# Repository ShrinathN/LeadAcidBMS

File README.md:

# LeadAcidBMS
A BMS for my lead acid battery.

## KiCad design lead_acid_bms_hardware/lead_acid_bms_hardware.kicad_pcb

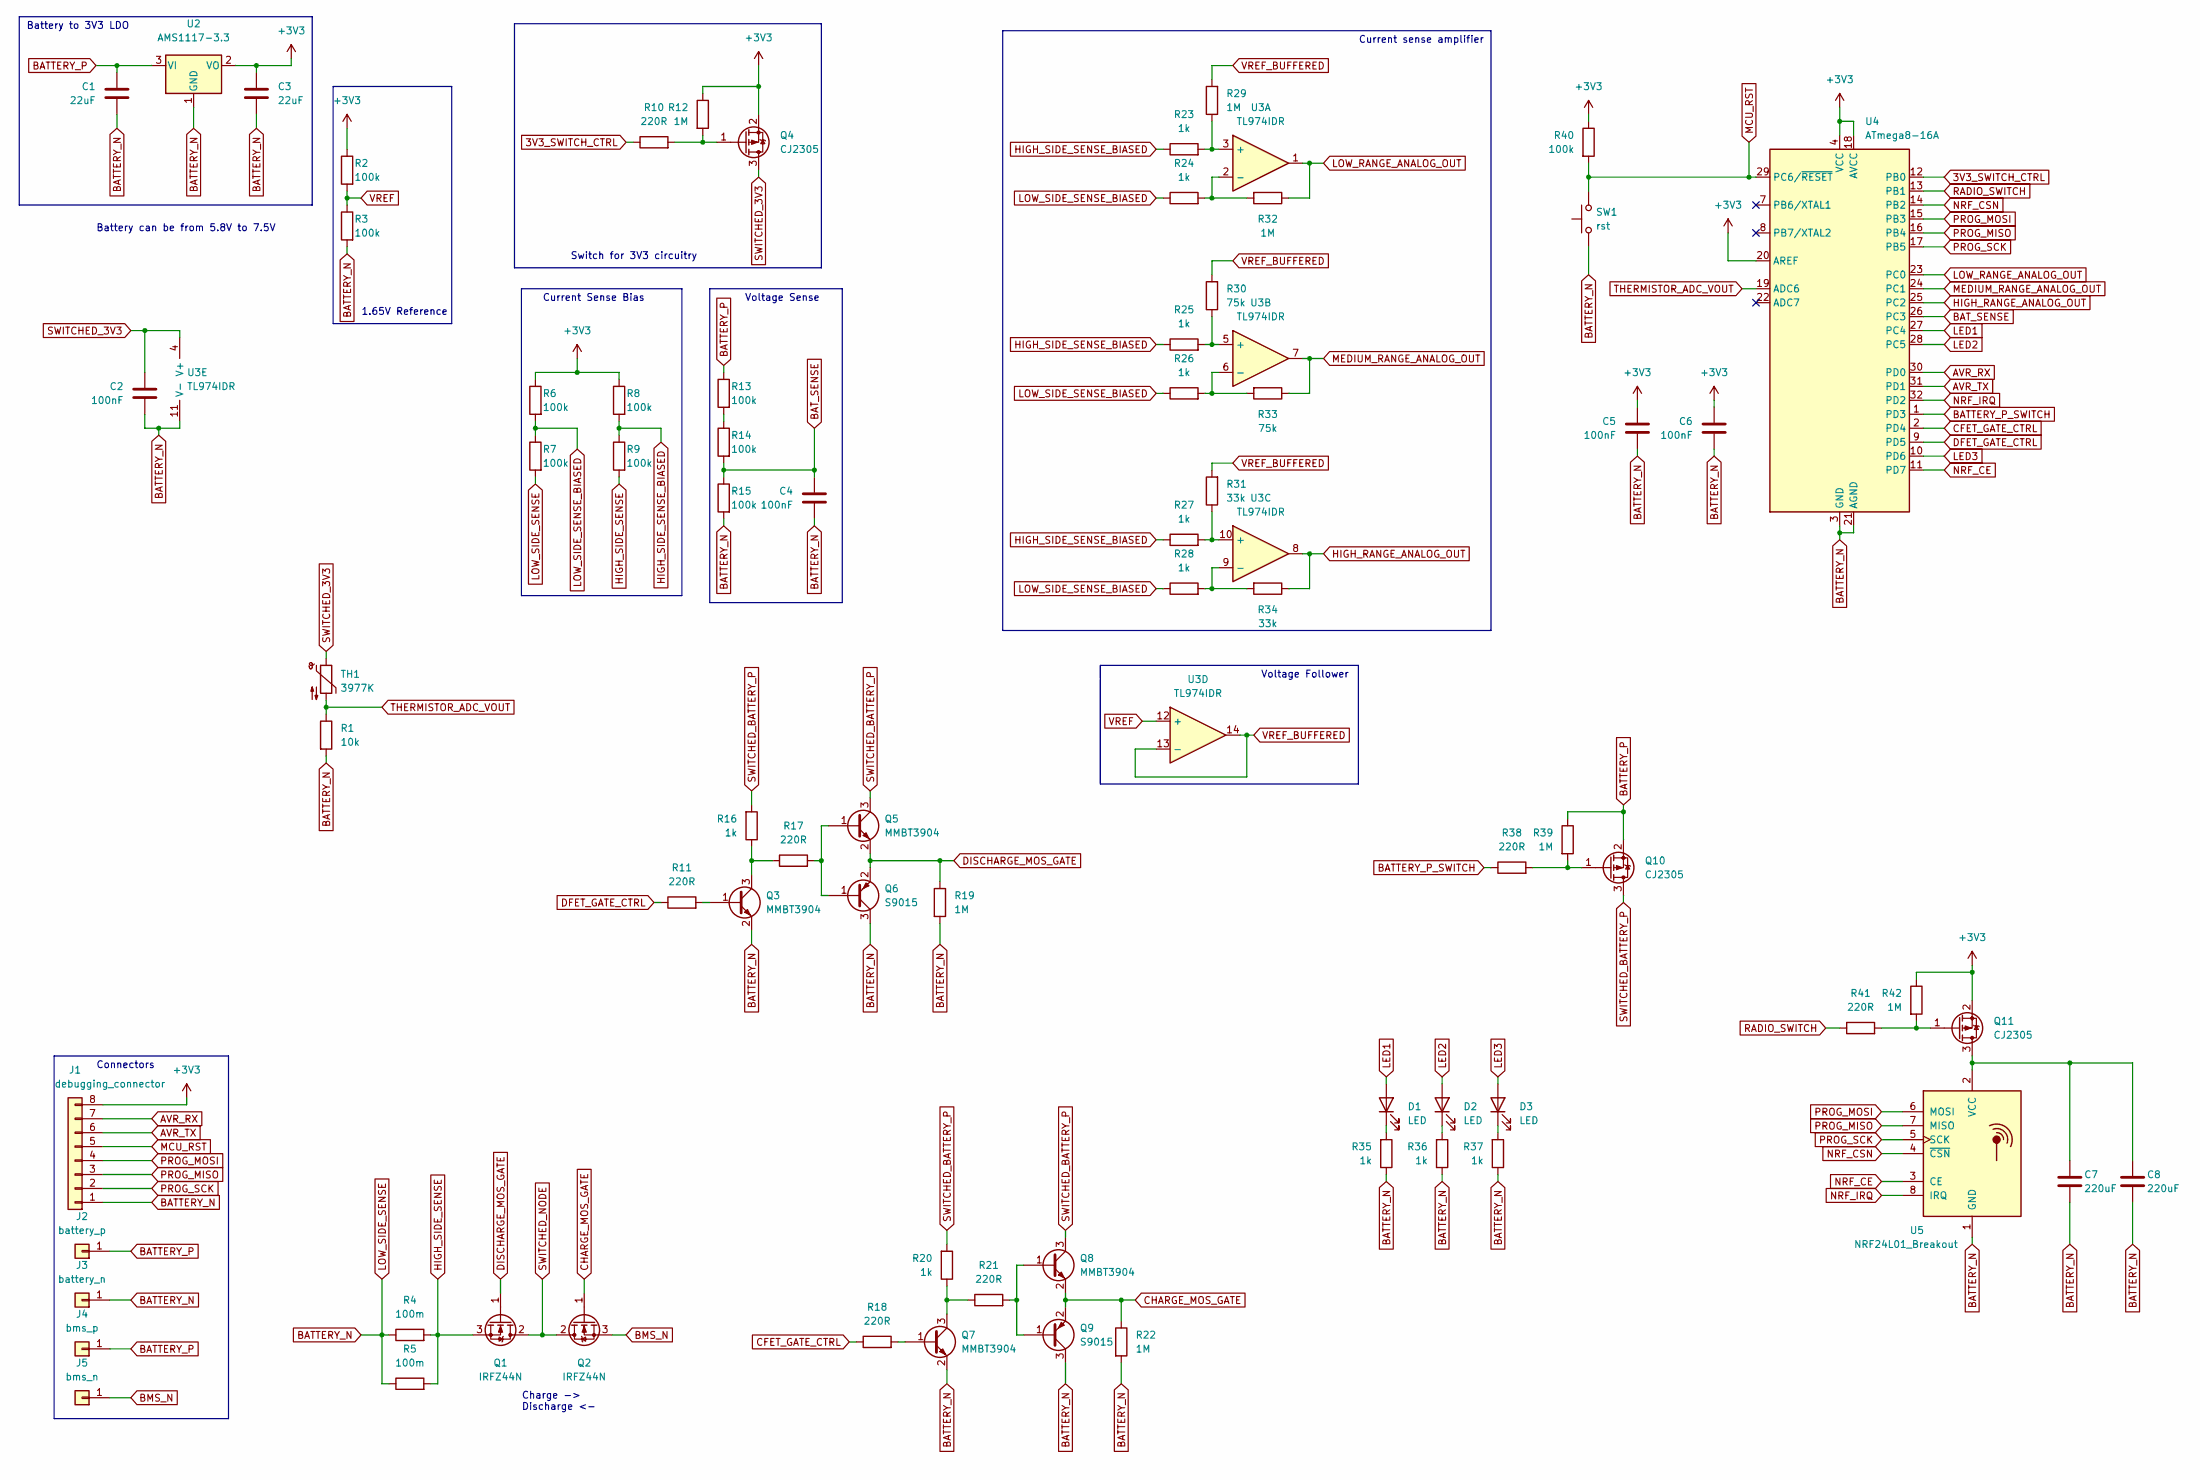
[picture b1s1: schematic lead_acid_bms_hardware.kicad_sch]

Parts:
C1, C3: 22uF; C_Radial_D5.0mm_H11.0mm_P2.00mm
C2, C4, C5, C6: 100nF; C_0805_2012Metric
C7, C8: 220uF; C_Radial_D6.3mm_H11.0mm_P2.50mm
D1, D2, D3: LED; LED_1206_3216Metric
J1: debugging_connector; PinHeader_1x08_P2.54mm_Vertical
J2: battery_p; MountingHole_3.2mm_M3_DIN965_Pad_TopBottom
J3: battery_n; MountingHole_3.2mm_M3_DIN965_Pad_TopBottom
J4: bms_p; MountingHole_3.2mm_M3_DIN965_Pad_TopBottom
J5: bms_n; MountingHole_3.2mm_M3_DIN965_Pad_TopBottom
Q1, Q2: IRFZ44N; TO-220-3_Horizontal_TabDown
Q3, Q5, Q7, Q8: MMBT3904; SOT-23
Q4, Q10, Q11: CJ2305; SOT-23
Q6, Q9: S9015; SOT-23
R1: 10k; R_0805_2012Metric
R2, R3, R6, R7, R8, R9, R13, R14, R15, R40: 100k; R_0805_2012Metric
R4, R5: 100m; R_2512_6332Metric
R10, R11, R17, R18, R21, R38, R41: 220R; R_0805_2012Metric
R12, R19, R22, R29, R32, R39, R42: 1M; R_0805_2012Metric
R16, R20, R23, R24, R25, R26, R27, R28, R35, R36, R37: 1k; R_0805_2012Metric
R30, R33: 75k; R_0805_2012Metric
R31, R34: 33k; R_0805_2012Metric
SW1: rst; SW_SPST_TL3342
TH1: 3977K; PinSocket_1x02_P2.54mm_Vertical
U2: AMS1117-3.3; SOT-223-3_TabPin2
U3: TL974IDR; TSSOP-14_4.4x5mm_P0.65mm
U4: ATmega8-16A; TQFP-32_7x7mm_P0.8mm
U5: NRF24L01_Breakout; nRF24L01_Breakout

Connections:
3V3_SWITCH_CTRL: R10.1, U4.12 (PB0)
+3V3: C3.1, C5.2, C6.2, J1.8, Q4.2 (S), Q11.2 (S), R2.1, R6.1, R8.1, R12.1, R40.1, R42.1, U2.2 (VO), U4.4 (VCC), U4.6 (VCC), U4.18 (AVCC), U4.20 (AREF)
AVR_RX: J1.7, U4.30 (PD0)
AVR_TX: J1.6, U4.31 (PD1)
BATTERY_N: C1.1, C2.1, C3.2, C4.1, C5.1, C6.1, C7.2, C8.2, J1.1, J3.1, Q3.2 (E), Q6.3 (C), Q7.2 (E), Q9.3 (C), R1.2, R3.2, R4.1, R5.1, R7.2, R15.2, R19.2, R22.2, R35.1, R36.1, R37.1, SW1.1, U2.1 (GND), U3.11 (V-), U4.3 (GND), U4.5 (GND), U4.21 (AGND), U5.1 (GND)
BATTERY_P: C1.2, J2.1, J4.1, Q10.2 (S), R13.1, R39.1, U2.3 (VI)
BATTERY_P_SWITCH: R38.1, U4.1 (PD3)
BAT_SENSE: C4.2, R14.2, R15.1, U4.26 (PC3)
BMS_N: J5.1, Q2.3 (S)
CFET_GATE_CTRL: R18.1, U4.2 (PD4)
CHARGE_MOS_GATE: Q2.1 (G), Q8.2 (E), Q9.2 (E), R22.1
DFET_GATE_CTRL: R11.1, U4.9 (PD5)
DISCHARGE_MOS_GATE: Q1.1 (G), Q5.2 (E), Q6.2 (E), R19.1
HIGH_RANGE_ANALOG_OUT: R34.1, U3.8, U4.25 (PC2)
HIGH_SIDE_SENSE: Q1.3 (S), R4.2, R5.2, R9.2
HIGH_SIDE_SENSE_BIASED: R8.2, R9.1, R23.1, R25.1, R27.1
LED1: D1.2 (A), U4.27 (PC4)
LED2: D2.2 (A), U4.28 (PC5)
LED3: D3.2 (A), U4.10 (PD6)
LOW_RANGE_ANALOG_OUT: R32.1, U3.1, U4.23 (PC0)
LOW_SIDE_SENSE_BIASED: R6.2, R7.1, R24.1, R26.1, R28.1
MCU_RST: J1.5, R40.2, SW1.2, U4.29 (PC6/~RESET)
MEDIUM_RANGE_ANALOG_OUT: R33.1, U3.7, U4.24 (PC1)
NRF_CE: U4.11 (PD7), U5.3 (CE)
NRF_CSN: U4.14 (PB2), U5.4 (~CSN)
NRF_IRQ: U4.32 (PD2), U5.8 (IRQ)
unnamed: C7.1, C8.1, Q11.3 (D), U5.2 (VCC)
unnamed: D1.1 (K), R35.2
unnamed: D2.1 (K), R36.2
unnamed: D3.1 (K), R37.2
unnamed: Q3.1 (B), R11.2
unnamed: Q3.3 (C), R16.1, R17.1
unnamed: Q4.1 (G), R10.2, R12.2
unnamed: Q5.1 (B), Q6.1 (B), R17.2
unnamed: Q7.1 (B), R18.2
unnamed: Q7.3 (C), R20.1, R21.1
unnamed: Q8.1 (B), Q9.1 (B), R21.2
unnamed: Q10.1 (G), R38.2, R39.2
unnamed: Q11.1 (G), R41.2, R42.2
unnamed: R13.2, R14.1
unnamed: R23.2, R29.1, U3.3 (+)
unnamed: R24.2, R32.2, U3.2 (-)
unnamed: R25.2, R30.1, U3.5 (+)
unnamed: R26.2, R33.2, U3.6 (-)
unnamed: R27.2, R31.1, U3.10 (+)
unnamed: R28.2, R34.2, U3.9 (-)
PROG_MISO: J1.3, U4.16 (PB4), U5.7 (MISO)
PROG_MOSI: J1.4, U4.15 (PB3), U5.6 (MOSI)
PROG_SCK: J1.2, U4.17 (PB5), U5.5 (SCK)
RADIO_SWITCH: R41.1, U4.13 (PB1)
SWITCHED_3V3: C2.2, Q4.3 (D), TH1.1, U3.4 (V+)
SWITCHED_BATTERY_P: Q5.3 (C), Q8.3 (C), Q10.3 (D), R16.2, R20.2
SWITCHED_NODE: Q1.2 (D), Q2.2 (D)
THERMISTOR_ADC_VOUT: R1.1, TH1.2, U4.19 (ADC6)
VREF: R2.2, R3.1, U3.12 (+)
VREF_BUFFERED: R29.2, R30.2, R31.2, U3.13 (-), U3.14

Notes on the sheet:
1.65V Reference
Voltage Follower
Current sense amplifier
Voltage Sense
Switch for 3V3 circuitry
Connectors
Charge -> Discharge <-
Battery can be from 5.8V to 7.5V
Current Sense Bias
Battery to 3V3 LDO

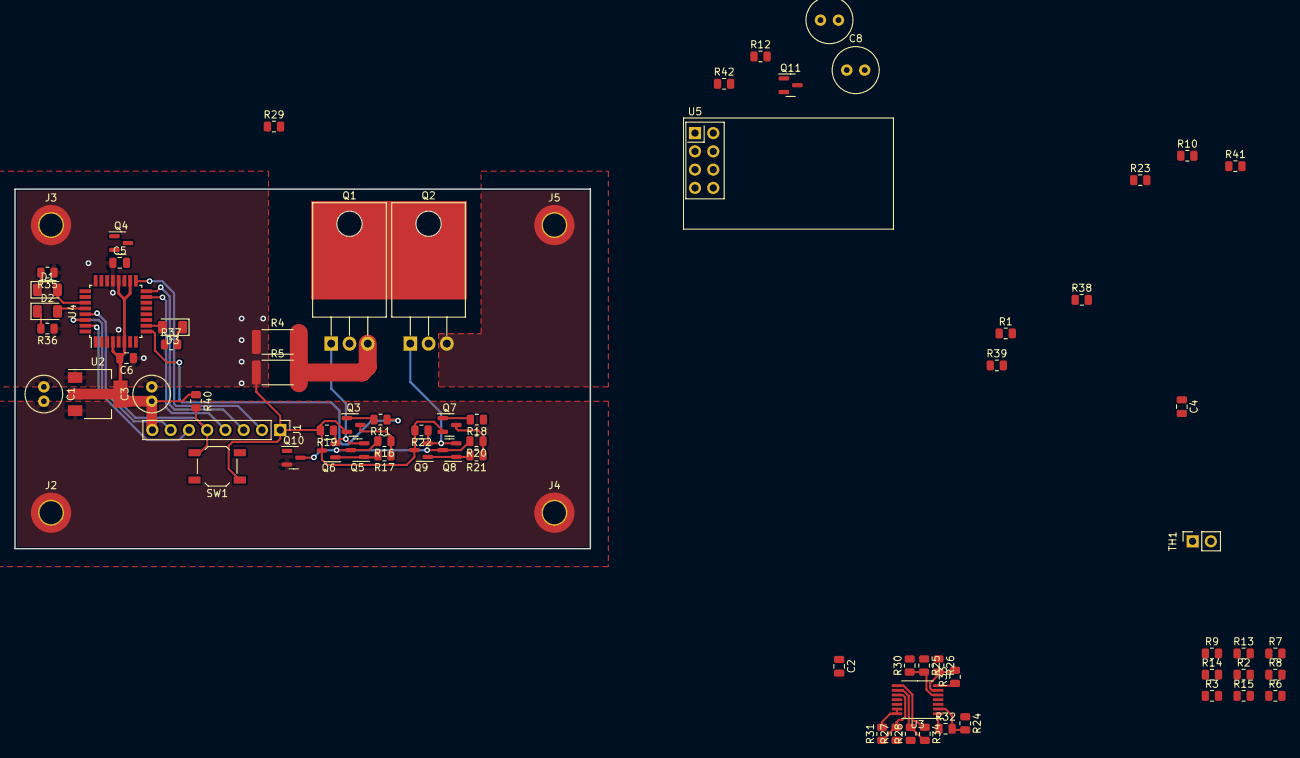
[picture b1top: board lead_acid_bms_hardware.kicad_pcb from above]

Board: 2 copper layers, 80.0 x 50.0 mm, 75 parts (0 on the bottom side), 56 nets.

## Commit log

2023-01-08 Added files
2023-01-08 Added NTC for temperature measurements
2023-01-08 Added 6V AGM battery STEP file
2023-01-15 Routing...
2023-01-15 Almost done with PCB placement/routing. Need to find lower power amplifier (TL974IDR is not good enough)
